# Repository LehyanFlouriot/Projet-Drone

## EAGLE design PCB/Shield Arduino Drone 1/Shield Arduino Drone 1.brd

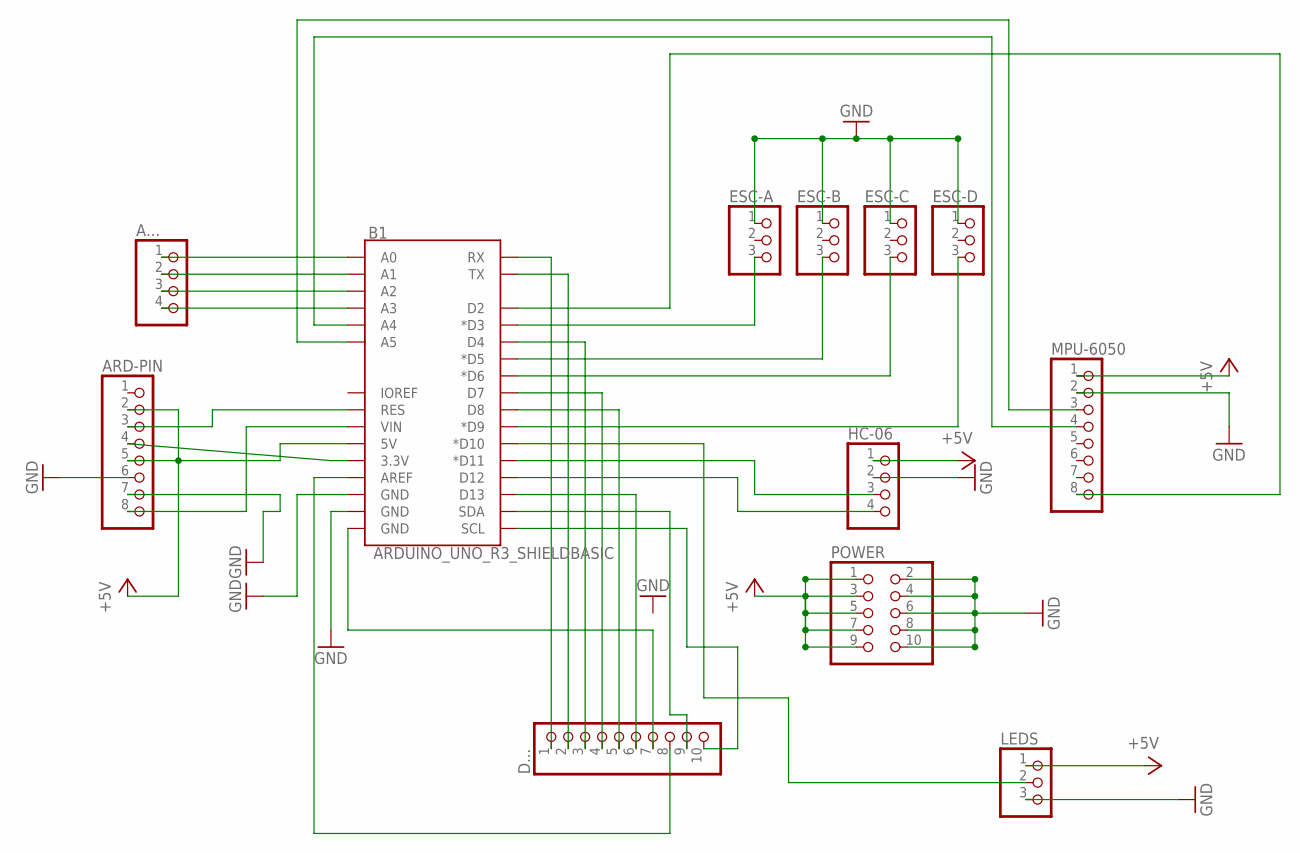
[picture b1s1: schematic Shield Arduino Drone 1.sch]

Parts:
A...: PINHD-1X4; 1X04
ARD-PIN: PINHD-1X8; 1X08
B1: ARDUINO_UNO_R3_SHIELDBASIC; UNO_R3_SHIELD
D...: PINHD-1X10; 1X10
ESC-A: PINHD-1X3; 1X03
ESC-B: PINHD-1X3; 1X03
ESC-C: PINHD-1X3; 1X03
ESC-D: PINHD-1X3; 1X03
HC-06: PINHD-1X4; 1X04
LEDS: PINHD-1X3; 1X03
MPU-6050: PINHD-1X8; 1X08
POWER: PINHD-2X5; 2X05

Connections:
+5V: ARD-PIN.2, ARD-PIN.5, B1.5V, HC-06.1, LEDS.1, MPU-6050.1, POWER.1, POWER.3, POWER.5, POWER.7, POWER.9
GND: ARD-PIN.6, ARD-PIN.7, B1.GND@1 (GND), B1.GND@2 (GND), ESC-A.1, ESC-B.1, ESC-C.1, ESC-D.1, HC-06.2, LEDS.3, MPU-6050.2, POWER.2, POWER.4, POWER.6, POWER.8, POWER.10
unnamed: B1.A5, MPU-6050.3
unnamed: B1.A4, MPU-6050.4
unnamed: B1.D2, MPU-6050.8
unnamed: B1.D11 (*D11), HC-06.3
unnamed: B1.D12, HC-06.4
unnamed: A....1, B1.A0
unnamed: A....2, B1.A1
unnamed: A....3, B1.A2
unnamed: A....4, B1.A3
unnamed: ARD-PIN.8, B1.VIN
unnamed: ARD-PIN.3, B1.RES
unnamed: B1.D13, D....6
unnamed: B1.RX, D....1
unnamed: ARD-PIN.4, B1.3.3V
unnamed: B1.TX, D....2
unnamed: B1.D3 (*D3), ESC-A.3
unnamed: B1.D4, D....3
unnamed: B1.D5 (*D5), ESC-B.3
unnamed: B1.D6 (*D6), ESC-C.3
unnamed: B1.D7, D....4
unnamed: B1.D8, D....5
unnamed: B1.D9 (*D9), ESC-D.3
unnamed: B1.D10 (*D10), LEDS.2
unnamed: B1.AREF, D....8
unnamed: B1.SDA, D....9
unnamed: B1.SCL, D....10
unnamed: B1.GND@0 (GND), D....7

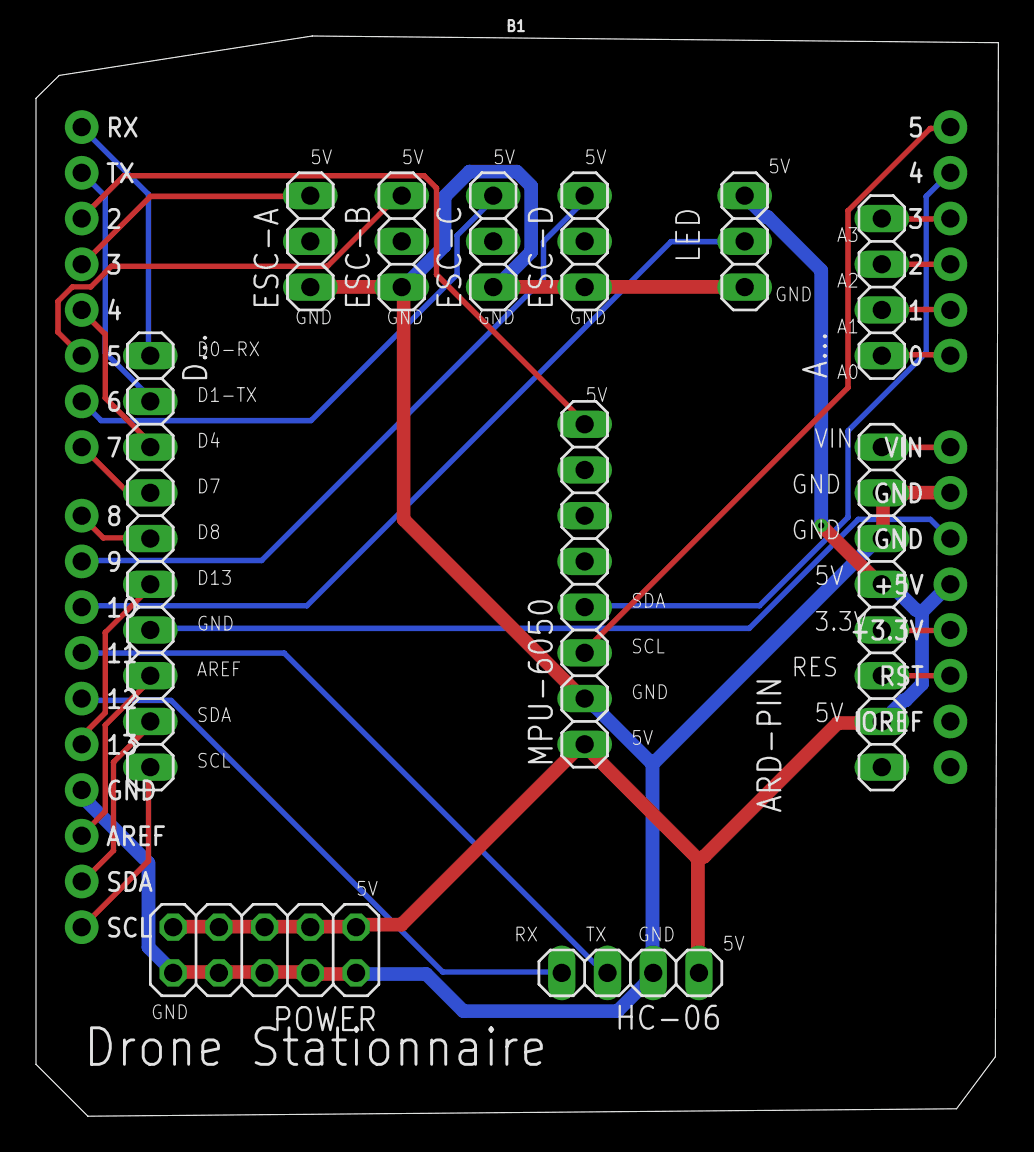
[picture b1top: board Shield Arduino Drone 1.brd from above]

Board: 2 copper layers, 53.5 x 60.0 mm, 12 parts (0 on the bottom side), 29 nets.

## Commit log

2019-12-04 Create Description du projet
2019-12-05 Update Description du projet

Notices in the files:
parts and their libraries:
SparkFun-Boards: Licensing: Creative Commons ShareAlike 4.0 International - https://creativecommons.org/licenses/by-sa/4.0
